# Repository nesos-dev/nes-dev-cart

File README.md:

# NES-DEV-CART

Open-source FPGA development cartridge for the Nintendo Entertainment System. **v4.1** — now with 8MB onboard PSRAM.

Plugs into a real NES. Programs over USB-C. Debug via UART. Full NES bus access. 39 SMT components, professionally assembled.

## What Is It

NES-DEV-CART is a cartridge-shaped PCB that replaces the ROM chip with a modern FPGA. It gives your FPGA bidirectional access to every signal on the NES 72-pin cartridge connector — CPU bus, PPU bus, CIC, expansion port — all level-shifted between 5V and 3.3V.

An onboard FT2232HL provides USB-C JTAG programming and UART debug console. No external programmer needed.

## Specs

| | |
|---|---|
| **FPGA** | Sipeed Tang Primer 25K (Gowin GW5A-25, 25K LUTs) |
| **ROM Storage** | 8MB SPI PSRAM |
| **USB** | FT2232HL — Ch.A: JTAG, Ch.B: UART debug |
| **Level Shifting** | 4x 74ALVC164245DGG (bidirectional 5V-3.3V) |
| **NES Signals** | CPU A0-A14, D0-D7, PPU A0-A13, D0-D7, CIC, IRQ, EXP |
| **PCB** | 4-layer, 1.6mm, ENIG, gold fingers, L-shaped |
| **Connector** | 72-pin NES edge connector (30-degree bevel) |
| **FPGA Connection** | 2x DF40C-60DS 0.4mm B2B connectors |

## What You Can Build

- **Homebrew games** — test on real hardware, not emulators
- **Custom mappers** — design mapper chips in Verilog that never existed
- **Flash cartridge** — load ROMs from USB, run on real NES
- **Bus analyzer** — sniff CPU/PPU traffic in real time via UART
- **Expansion audio** — VRC6, Sunsoft 5B style audio hardware
- **Hardware research** — study NES bus behavior at the signal level

## Repository Structure

```
hardware/
├── nes-dev-cart.kicad_pcb      KiCad PCB layout
├── nes-dev-cart.kicad_sch      KiCad schematic
├── nes-dev-cart.kicad_pro      KiCad project
├── footprints/                 Custom footprint libraries
├── shell/                     Cart shell STL files (front/back)
└── production/
    ├── nes-dev-cart-gerbers.zip    Fabrication-ready gerbers
    ├── nes-dev-cart-bom.csv        BOM with LCSC part numbers
    ├── nes-dev-cart-cpl-jlcpcb.csv Component placement list
    ├── README-assembly.md          Assembly instructions
    ├── nes-dev-cart-render-*.png   Board renders (top/bottom)
    └── gerbers/                    Individual gerber files

website/                        Product website (nesos.dev)
├── index.html
├── style.css
└── success.html
```

## Ordering PCBs

Upload `hardware/production/nes-dev-cart-gerbers.zip` to JLCPCB:

- Layers: 4
- Thickness: 1.6mm
- Surface finish: ENIG
- Gold fingers: Yes, 30-degree bevel
- Assembly: Both sides (DF40 connectors on bottom)

Upload `nes-dev-cart-bom.csv` and `nes-dev-cart-cpl-jlcpcb.csv` for SMT assembly. See `production/README-assembly.md` for details.

## Requirements

- NES front-loader console (NES-001)
- Sipeed Tang Primer 25K module
- USB-C cable
- Gowin IDE or Yosys/nextpnr for FPGA development

## License

Hardware: GPL-3.0

NES-DEV-CART is an independent project not affiliated with or endorsed by Nintendo.

## Links

- Website: https://nesos.dev

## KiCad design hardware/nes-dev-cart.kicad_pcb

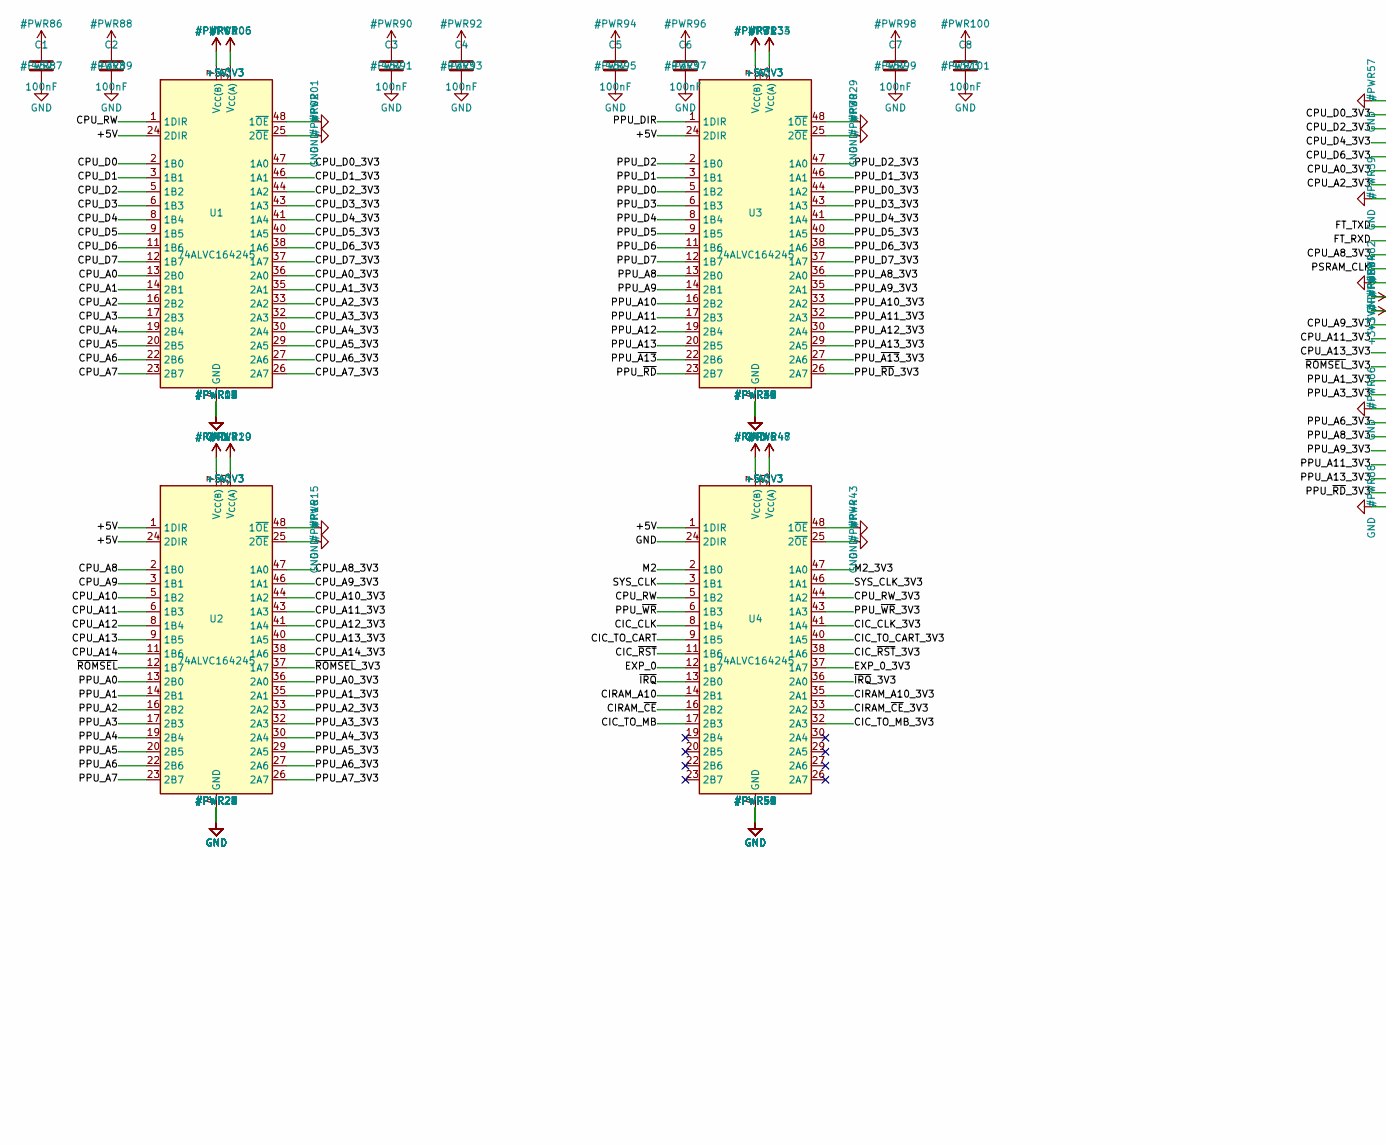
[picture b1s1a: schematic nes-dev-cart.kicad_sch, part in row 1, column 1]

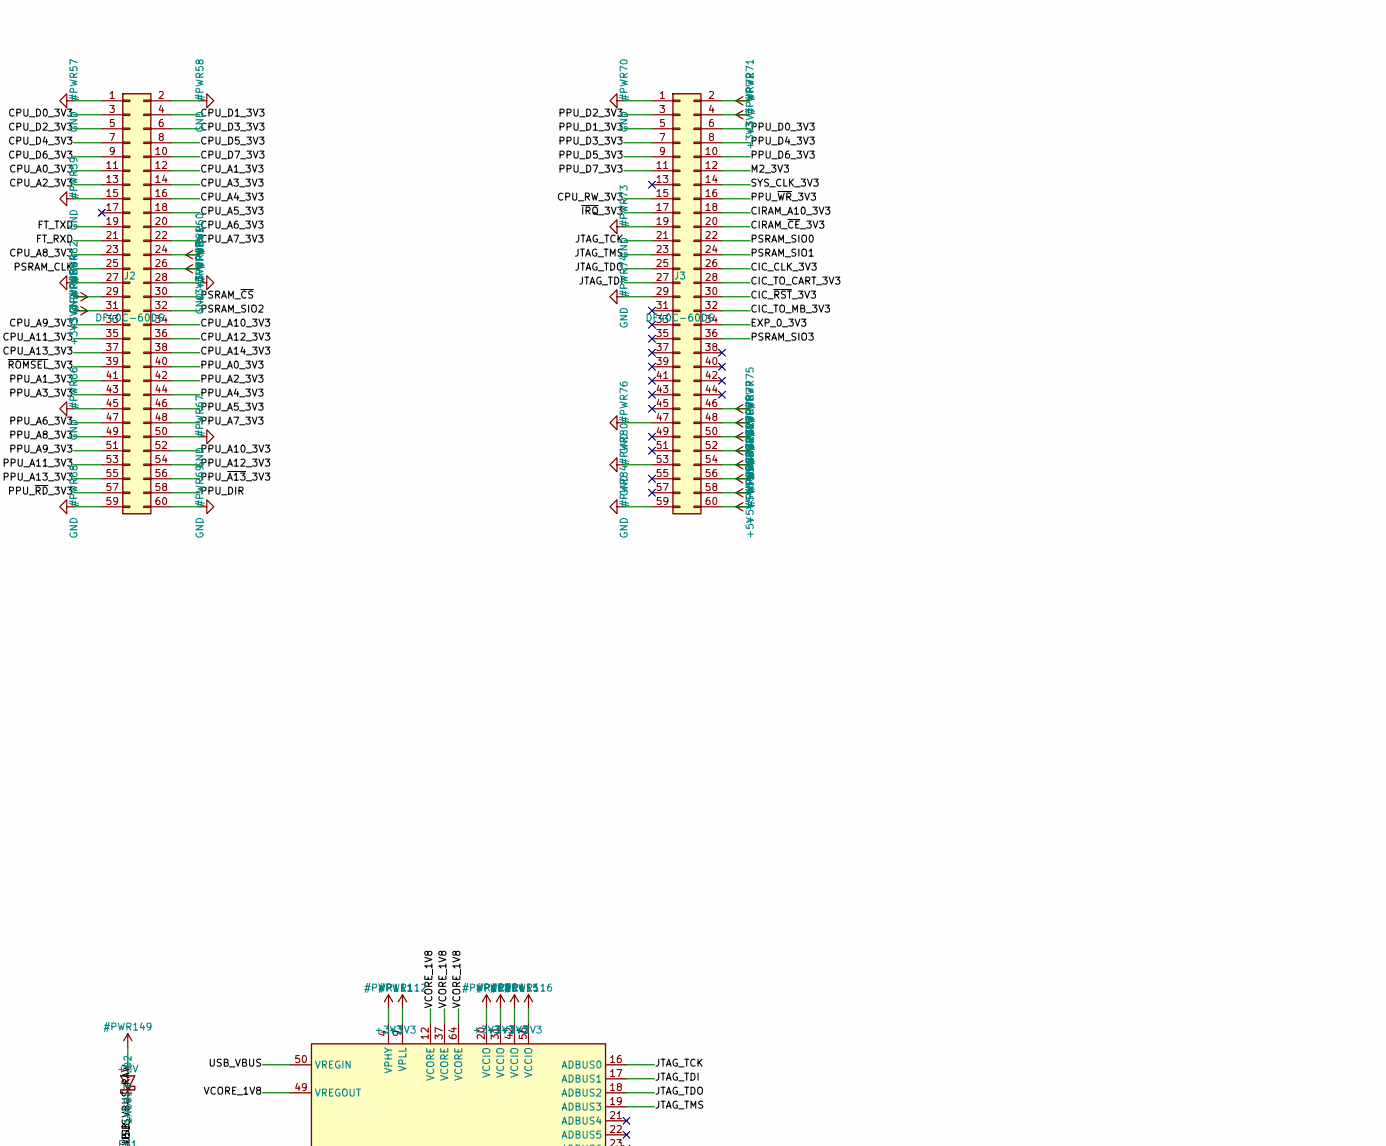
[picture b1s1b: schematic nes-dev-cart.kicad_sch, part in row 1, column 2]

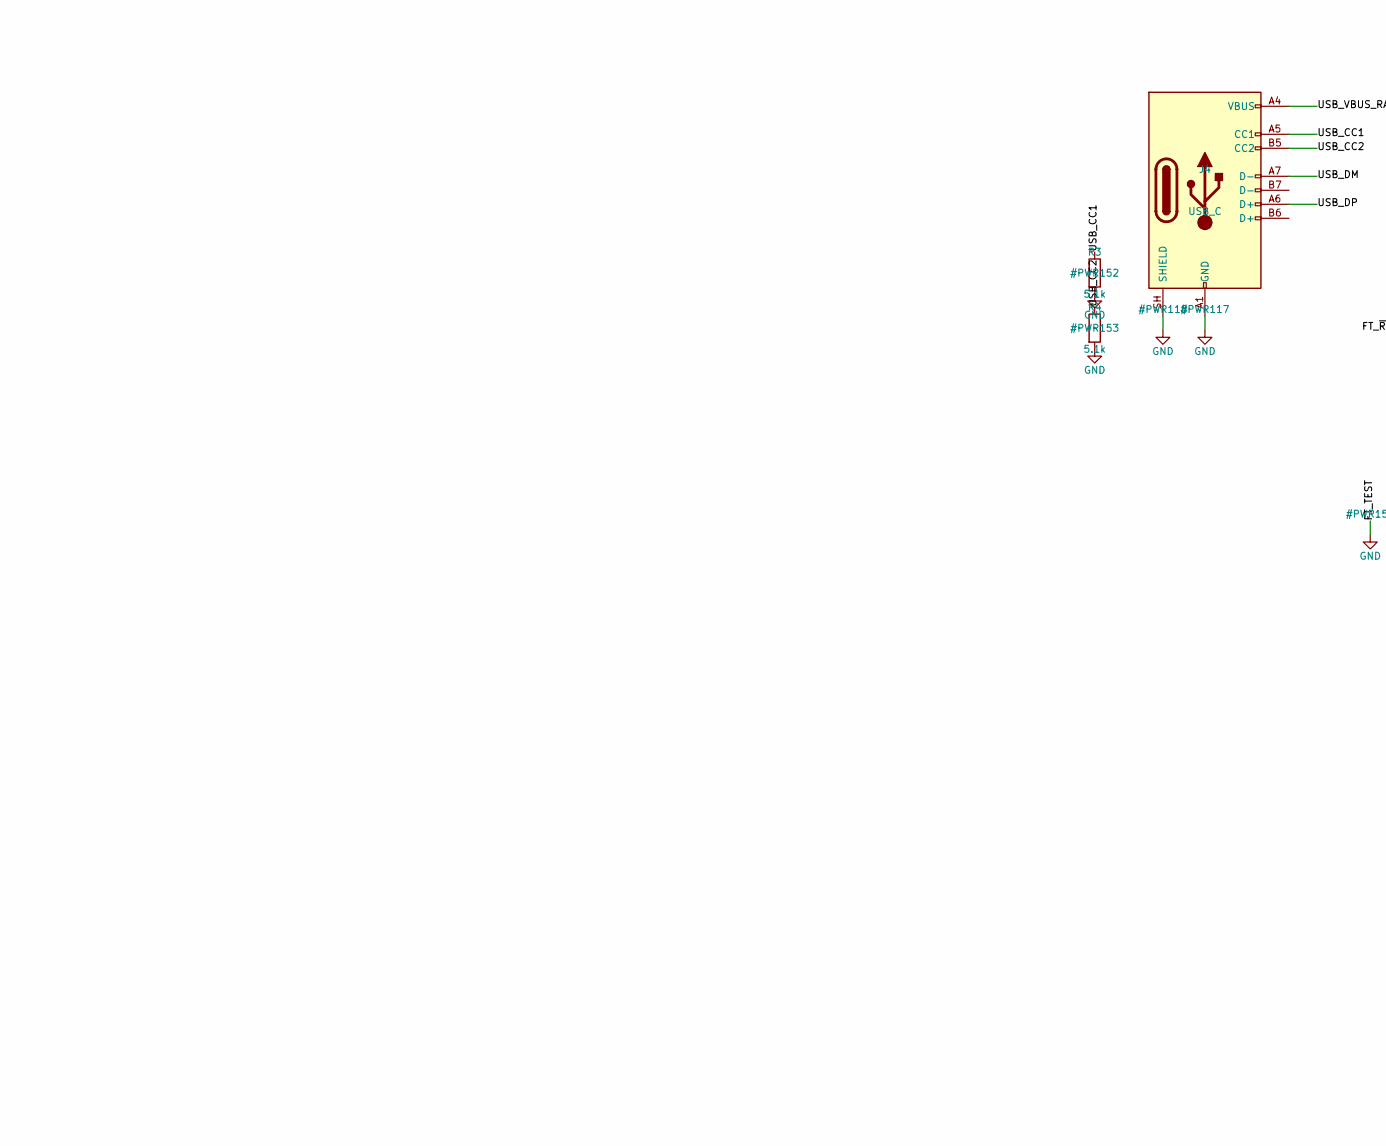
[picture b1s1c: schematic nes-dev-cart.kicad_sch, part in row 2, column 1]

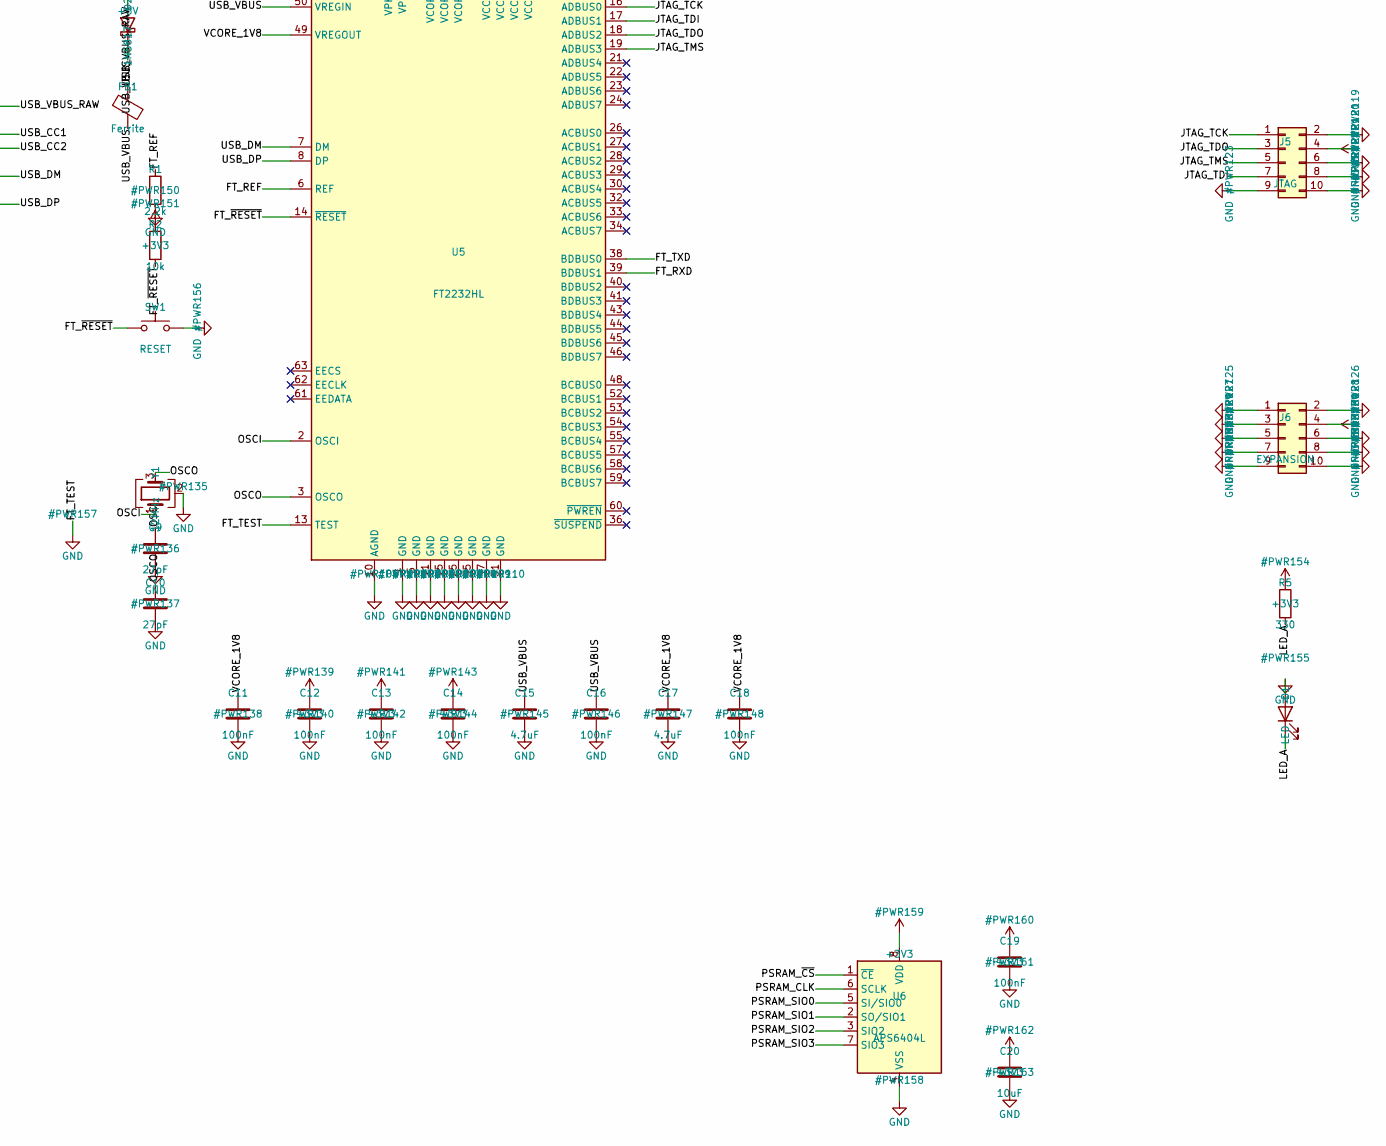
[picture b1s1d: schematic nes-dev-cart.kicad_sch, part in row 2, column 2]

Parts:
C1, C2, C3, C4, C5, C6, C7, C8, C11, C12, C13, C14, C16, C18, C19: 100nF
C9, C10: 27pF
C15, C17: 4.7uF
C20: 10uF
D1: LED
D2: 1N5817
FB1: Ferrite
J2, J3: DF40C-60DS
J4: USB_C
J5: JTAG
J6: EXPANSION
R1: 2.2k
R2: 10k
R3, R4: 5.1k
R5: 330
SW1: RESET
U1, U2, U3, U4: 74ALVC164245
U5: FT2232HL
U6: APS6404L
Y1: 12MHz

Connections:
+3V3: C2.1, C4.1, C6.1, C8.1, C12.1, C13.1, C14.1, C19.1, C20.1, J2.24, J2.26, J2.29, J2.31, J3.2, J3.4, J3.46, J3.48, J3.50, J5.4, J6.4, R2.1, R5.1, U1.31 (V_{CC(A)}), U1.42 (V_{CC(A)}), U2.31 (V_{CC(A)}), U2.42 (V_{CC(A)}), U3.31 (V_{CC(A)}), U3.42 (V_{CC(A)}), U4.31 (V_{CC(A)}), U4.42 (V_{CC(A)}), U5.4 (VPHY), U5.9 (VPLL), U5.20 (VCCIO), U5.31 (VCCIO), U5.42 (VCCIO), U5.56 (VCCIO), U6.8 (VDD)
+5V: C1.1, C3.1, C5.1, C7.1, D2.2 (A), J3.52, J3.54, J3.56, J3.58, J3.60, U1.7 (V_{CC(B)}), U1.18 (V_{CC(B)}), U1.24 (2DIR), U2.1 (1DIR), U2.7 (V_{CC(B)}), U2.18 (V_{CC(B)}), U2.24 (2DIR), U3.7 (V_{CC(B)}), U3.18 (V_{CC(B)}), U3.24 (2DIR), U4.1 (1DIR), U4.7 (V_{CC(B)}), U4.18 (V_{CC(B)}); also elsewhere on the board
/CIC_CLK: U4.8 (1B4); also elsewhere on the board
/CIC_CLK_3V3: J3.26, U4.41 (1A4)
/CIC_TO_CART: U4.9 (1B5); also elsewhere on the board
/CIC_TO_CART_3V3: J3.28, U4.40 (1A5)
/CIC_TO_MB: U4.17 (2B3); also elsewhere on the board
/CIC_TO_MB_3V3: J3.32, U4.32 (2A3)
/CIC_~RST: U4.11 (1B6); also elsewhere on the board
/CIC_~RST_3V3: J3.30, U4.38 (1A6)
/CIRAM_A10: U4.14 (2B1); also elsewhere on the board
/CIRAM_A10_3V3: J3.18, U4.35 (2A1)
/CIRAM_~CE: U4.16 (2B2); also elsewhere on the board
/CIRAM_~CE_3V3: J3.20, U4.33 (2A2)
/CPU_A0: U1.13 (2B0); also elsewhere on the board
/CPU_A0_3V3: J2.11, U1.36 (2A0)
/CPU_A1: U1.14 (2B1); also elsewhere on the board
/CPU_A1_3V3: J2.12, U1.35 (2A1)
/CPU_A2: U1.16 (2B2); also elsewhere on the board
/CPU_A2_3V3: J2.13, U1.33 (2A2)
/CPU_A3: U1.17 (2B3); also elsewhere on the board
/CPU_A3_3V3: J2.14, U1.32 (2A3)
/CPU_A4: U1.19 (2B4); also elsewhere on the board
/CPU_A4_3V3: J2.16, U1.30 (2A4)
/CPU_A5: U1.20 (2B5); also elsewhere on the board
/CPU_A5_3V3: J2.18, U1.29 (2A5)
/CPU_A6: U1.22 (2B6); also elsewhere on the board
/CPU_A6_3V3: J2.20, U1.27 (2A6)
/CPU_A7: U1.23 (2B7); also elsewhere on the board
/CPU_A7_3V3: J2.22, U1.26 (2A7)
/CPU_A8: U2.2 (1B0); also elsewhere on the board
/CPU_A8_3V3: J2.23, U2.47 (1A0)
/CPU_A9: U2.3 (1B1); also elsewhere on the board
/CPU_A9_3V3: J2.33, U2.46 (1A1)
/CPU_A10: U2.5 (1B2); also elsewhere on the board
/CPU_A10_3V3: J2.34, U2.44 (1A2)
/CPU_A11: U2.6 (1B3); also elsewhere on the board
/CPU_A11_3V3: J2.35, U2.43 (1A3)
/CPU_A12: U2.8 (1B4); also elsewhere on the board
/CPU_A12_3V3: J2.36, U2.41 (1A4)
/CPU_A13: U2.9 (1B5); also elsewhere on the board
/CPU_A13_3V3: J2.37, U2.40 (1A5)
/CPU_A14: U2.11 (1B6); also elsewhere on the board
/CPU_A14_3V3: J2.38, U2.38 (1A6)
/CPU_D0: U1.2 (1B0); also elsewhere on the board
/CPU_D0_3V3: J2.3, U1.47 (1A0)
/CPU_D1: U1.3 (1B1); also elsewhere on the board
/CPU_D1_3V3: J2.4, U1.46 (1A1)
/CPU_D2: U1.5 (1B2); also elsewhere on the board
/CPU_D2_3V3: J2.5, U1.44 (1A2)
/CPU_D3: U1.6 (1B3); also elsewhere on the board
/CPU_D3_3V3: J2.6, U1.43 (1A3)
/CPU_D4: U1.8 (1B4); also elsewhere on the board
/CPU_D4_3V3: J2.7, U1.41 (1A4)
/CPU_D5: U1.9 (1B5); also elsewhere on the board
/CPU_D5_3V3: J2.8, U1.40 (1A5)
/CPU_D6: U1.11 (1B6); also elsewhere on the board
/CPU_D6_3V3: J2.9, U1.38 (1A6)
/CPU_D7: U1.12 (1B7); also elsewhere on the board
/CPU_D7_3V3: J2.10, U1.37 (1A7)
/CPU_RW: U1.1 (1DIR), U4.5 (1B2); also elsewhere on the board
/CPU_RW_3V3: J3.15, U4.44 (1A2)
/EXP_0: U4.12 (1B7); also elsewhere on the board
/EXP_0_3V3: J3.34, U4.37 (1A7)
/FT_REF: R1.1, U5.6 (REF)
/FT_RXD: J2.21, U5.39 (BDBUS1)
/FT_TXD: J2.19, U5.38 (BDBUS0)
/FT_~RESET: R2.2, SW1.1, U5.14 (~RESET)
/JTAG_TCK: J3.21, J5.1, U5.16 (ADBUS0)
/JTAG_TDI: J3.27, J5.7, U5.17 (ADBUS1)
/JTAG_TDO: J3.25, J5.3, U5.18 (ADBUS2)
/JTAG_TMS: J3.23, J5.5, U5.19 (ADBUS3)
/LED_A: D1.1 (K), R5.2
/M2: U4.2 (1B0); also elsewhere on the board
/M2_3V3: J3.12, U4.47 (1A0)
/OSCI: C9.1, U5.2 (OSCI), Y1.1
/OSCO: C10.1, U5.3 (OSCO), Y1.3
/PPU_A0: U2.13 (2B0); also elsewhere on the board
/PPU_A0_3V3: J2.40, U2.36 (2A0)
/PPU_A1: U2.14 (2B1); also elsewhere on the board
/PPU_A1_3V3: J2.41, U2.35 (2A1)
/PPU_A2: U2.16 (2B2); also elsewhere on the board
/PPU_A2_3V3: J2.42, U2.33 (2A2)
/PPU_A3: U2.17 (2B3); also elsewhere on the board
/PPU_A3_3V3: J2.43, U2.32 (2A3)
/PPU_A4: U2.19 (2B4); also elsewhere on the board
/PPU_A4_3V3: J2.44, U2.30 (2A4)
/PPU_A5: U2.20 (2B5); also elsewhere on the board
/PPU_A5_3V3: J2.46, U2.29 (2A5)
/PPU_A6: U2.22 (2B6); also elsewhere on the board
/PPU_A6_3V3: J2.47, U2.27 (2A6)
/PPU_A7: U2.23 (2B7); also elsewhere on the board
/PPU_A7_3V3: J2.48, U2.26 (2A7)
/PPU_A8: U3.13 (2B0); also elsewhere on the board
/PPU_A8_3V3: J2.49, U3.36 (2A0)
/PPU_A9: U3.14 (2B1); also elsewhere on the board
/PPU_A9_3V3: J2.51, U3.35 (2A1)
/PPU_A10: U3.16 (2B2); also elsewhere on the board
/PPU_A10_3V3: J2.52, U3.33 (2A2)
/PPU_A11: U3.17 (2B3); also elsewhere on the board
/PPU_A11_3V3: J2.53, U3.32 (2A3)
/PPU_A12: U3.19 (2B4); also elsewhere on the board
/PPU_A12_3V3: J2.54, U3.30 (2A4)
/PPU_A13: U3.20 (2B5); also elsewhere on the board
/PPU_A13_3V3: J2.55, U3.29 (2A5)
/PPU_D0: U3.5 (1B2); also elsewhere on the board
/PPU_D0_3V3: J3.6, U3.44 (1A2)
/PPU_D1: U3.3 (1B1); also elsewhere on the board
/PPU_D1_3V3: J3.5, U3.46 (1A1)
/PPU_D2: U3.2 (1B0); also elsewhere on the board
/PPU_D2_3V3: J3.3, U3.47 (1A0)
/PPU_D3: U3.6 (1B3); also elsewhere on the board
/PPU_D3_3V3: J3.7, U3.43 (1A3)
/PPU_D4: U3.8 (1B4); also elsewhere on the board
/PPU_D4_3V3: J3.8, U3.41 (1A4)
/PPU_D5: U3.9 (1B5); also elsewhere on the board
/PPU_D5_3V3: J3.9, U3.40 (1A5)
/PPU_D6: U3.11 (1B6); also elsewhere on the board
/PPU_D6_3V3: J3.10, U3.38 (1A6)
/PPU_D7: U3.12 (1B7); also elsewhere on the board
/PPU_D7_3V3: J3.11, U3.37 (1A7)
/PPU_DIR: J2.58, U3.1 (1DIR)
/PPU_~A13: U3.22 (2B6); also elsewhere on the board
/PPU_~A13_3V3: J2.56, U3.27 (2A6)
/PPU_~RD: U3.23 (2B7); also elsewhere on the board
/PPU_~RD_3V3: J2.57, U3.26 (2A7)
/PPU_~WR: U4.6 (1B3); also elsewhere on the board
/PPU_~WR_3V3: J3.16, U4.43 (1A3)
/PSRAM_CLK: J2.25, U6.6 (SCLK)
/PSRAM_SIO0: J3.22, U6.5 (SI/SIO0)
/PSRAM_SIO1: J3.24, U6.2 (SO/SIO1)
/PSRAM_SIO2: J2.32, U6.3 (SIO2)
/PSRAM_SIO3: J3.36, U6.7 (SIO3)
/PSRAM_~CS: J2.30, U6.1 (~CE)
/SYS_CLK: U4.3 (1B1); also elsewhere on the board
/SYS_CLK_3V3: J3.14, U4.46 (1A1)
/USB_CC1: J4.A5 (CC1), R3.1
/USB_CC2: J4.B5 (CC2), R4.1
/USB_DM: J4.A7 (D-), U5.7 (DM)
/USB_DP: J4.A6 (D+), U5.8 (DP)
/USB_VBUS: C15.1, C16.1, D2.1 (K), FB1.2, U5.50 (VREGIN)
/USB_VBUS_RAW: FB1.1, J4.A4 (VBUS), J4.A9 (VBUS), J4.B4 (VBUS), J4.B9 (VBUS)
/VCORE_1V8: C11.1, C17.1, C18.1, U5.12 (VCORE), U5.37 (VCORE), U5.49 (VREGOUT), U5.64 (VCORE)
/~IRQ: U4.13 (2B0); also elsewhere on the board
/~IRQ_3V3: J3.17, U4.36 (2A0)
/~ROMSEL: U2.12 (1B7); also elsewhere on the board
/~ROMSEL_3V3: J2.39, U2.37 (1A7)
GND: C1.2, C2.2, C3.2, C4.2, C5.2, C6.2, C7.2, C8.2, C9.2, C10.2, C11.2, C12.2, C13.2, C14.2, C15.2, C16.2, C17.2, C18.2, C19.2, C20.2, D1.2 (A), J2.1, J2.2, J2.15, J2.27, J2.28, J2.45, J2.50, J2.59, J2.60, J3.1, J3.19, J3.29, J3.47, J3.53, J3.59, J4.A1 (GND), J4.A12 (GND), J4.B1 (GND), J4.B12 (GND), J4.SH (SHIELD), J5.2, J5.6, J5.8, J5.9, J5.10, J6.1, J6.2, J6.3, J6.5, J6.6, J6.7, J6.8, J6.9, J6.10, R1.2, R3.2, R4.2, SW1.2, U1.4 (GND), U1.10 (GND), U1.15 (GND), U1.21 (GND), U1.25 (2~OE), U1.28 (GND), U1.34 (GND), U1.39 (GND), U1.45 (GND), U1.48 (1~OE), U2.4 (GND), U2.10 (GND), U2.15 (GND), U2.21 (GND), U2.25 (2~OE), U2.28 (GND), U2.34 (GND), U2.39 (GND), U2.45 (GND), U2.48 (1~OE), U3.4 (GND), U3.10 (GND), U3.15 (GND), U3.21 (GND), U3.25 (2~OE), U3.28 (GND), U3.34 (GND), U3.39 (GND), U3.45 (GND), U3.48 (1~OE), U4.4 (GND), U4.10 (GND), U4.15 (GND), U4.21 (GND), U4.24 (2DIR), U4.25 (2~OE), U4.28 (GND), U4.34 (GND), U4.39 (GND), U4.45 (GND), U4.48 (1~OE), U5.1 (GND), U5.5 (GND), U5.10 (AGND), U5.11 (GND), U5.13 (TEST), U5.15 (GND), U5.25 (GND), U5.35 (GND), U5.47 (GND), U5.51 (GND), U6.4 (VSS), Y1.2 (G), Y1.4 (G); also elsewhere on the board

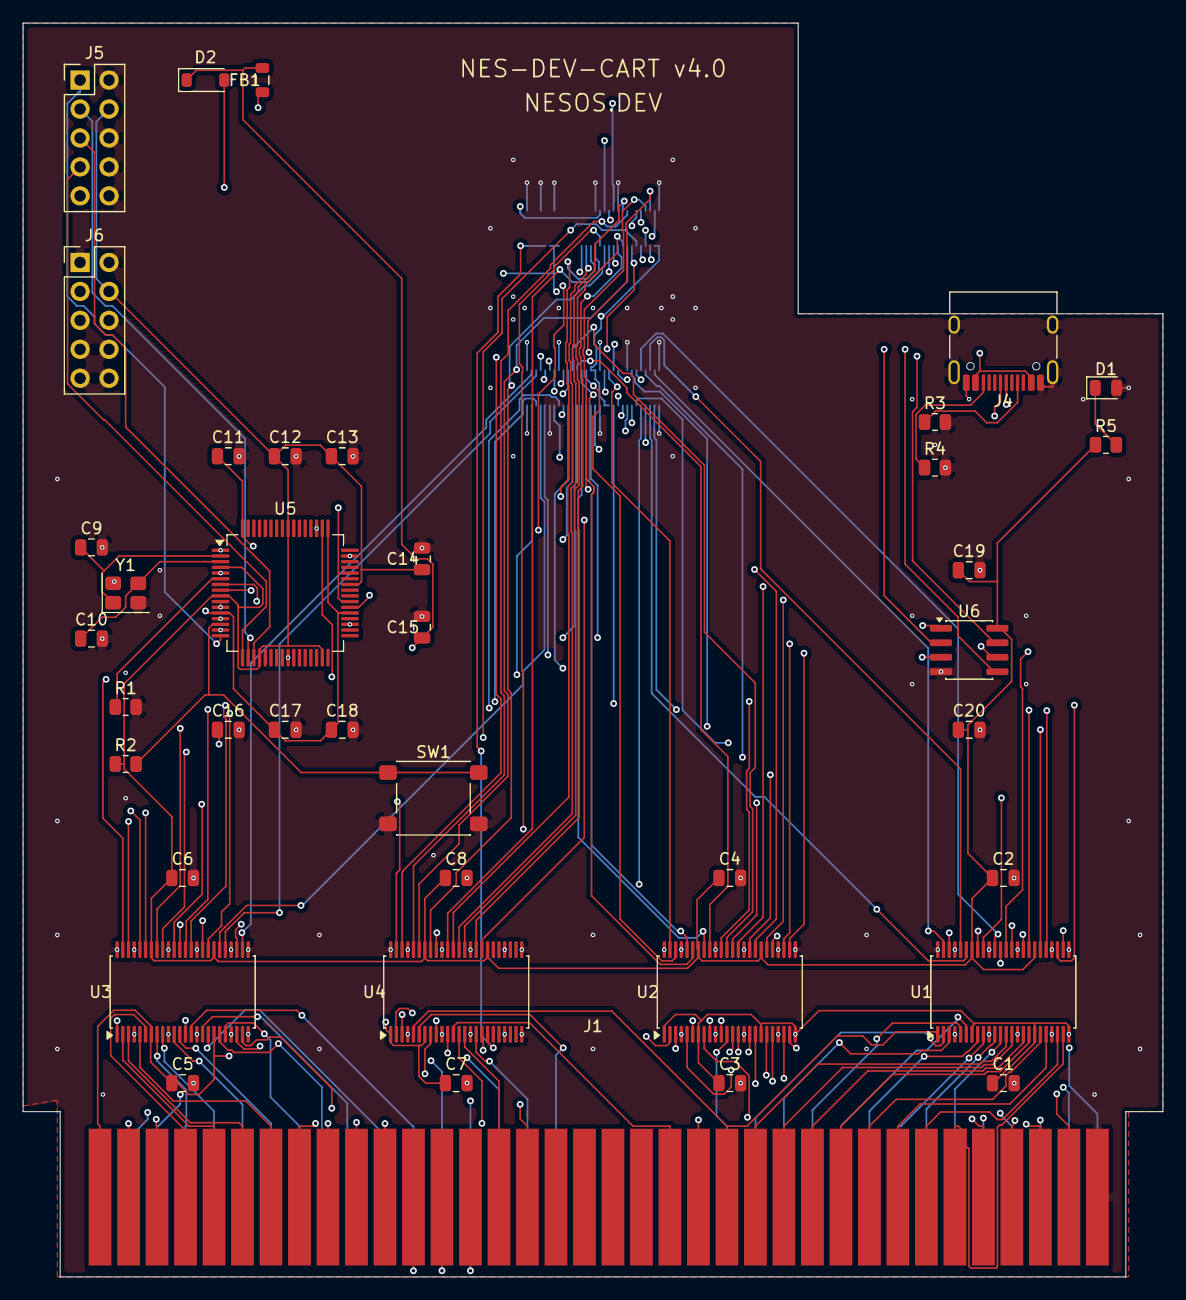
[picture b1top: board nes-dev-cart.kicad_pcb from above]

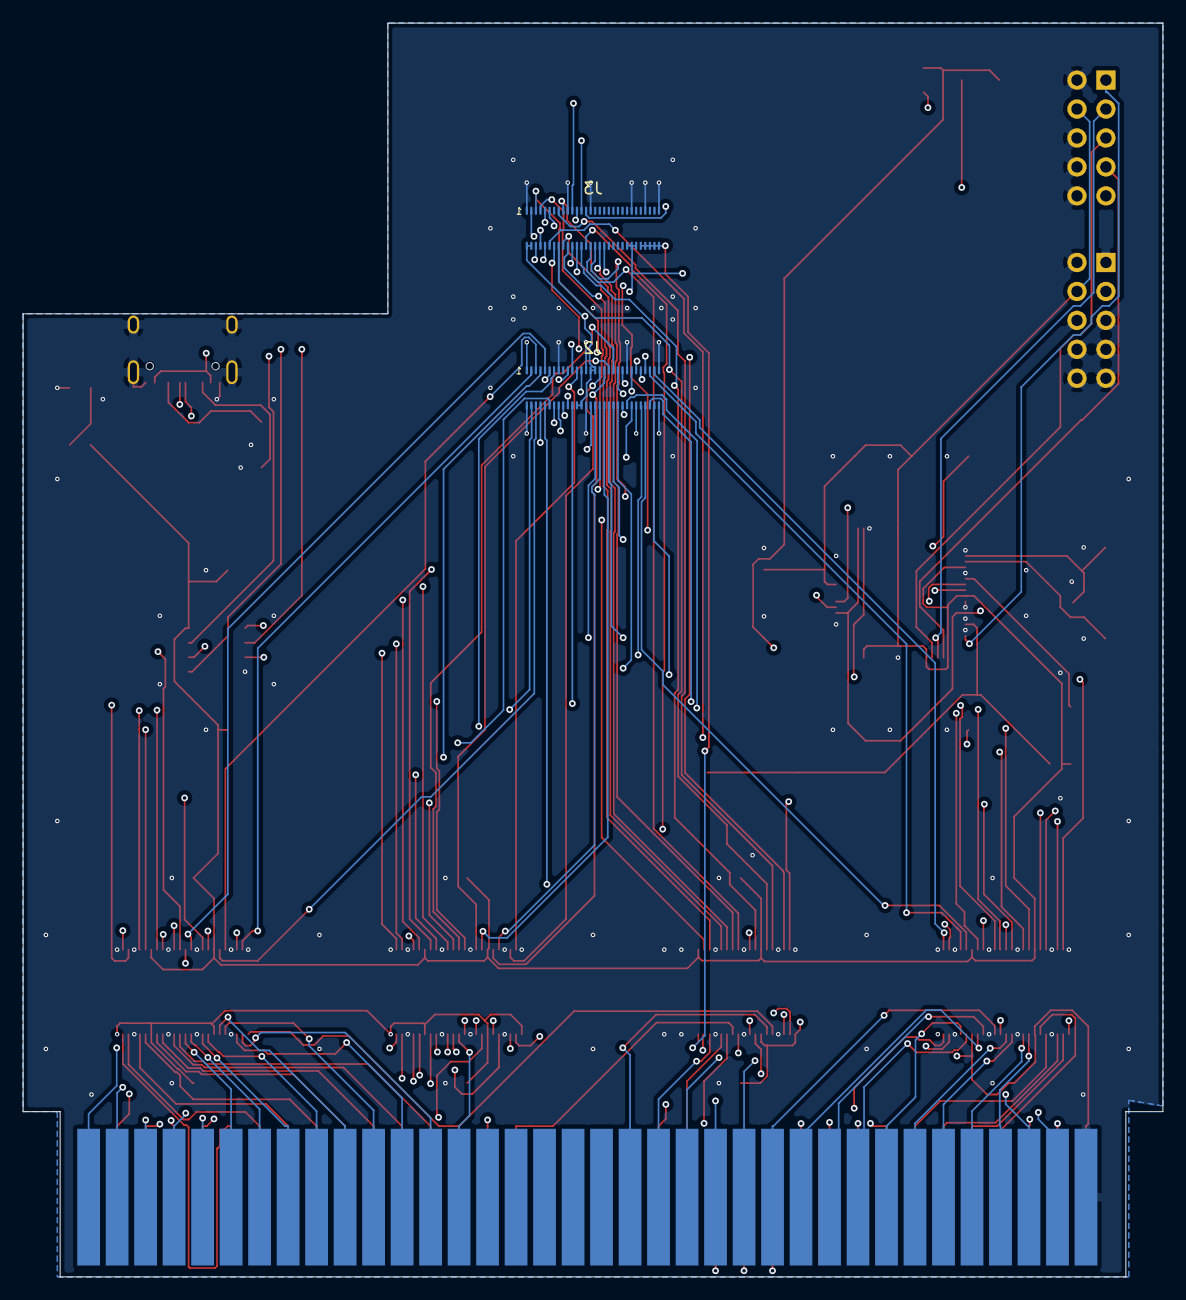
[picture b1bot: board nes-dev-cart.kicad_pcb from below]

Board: 4 copper layers, 100.0 x 110.0 mm, 42 parts (2 on the bottom side), 148 nets.

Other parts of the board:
J1: NES_72Pin; NES_72Pin_CardEdge

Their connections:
+5V: J1.36; also elsewhere on the board
/CIC_CLK: J1.70; also elsewhere on the board
/CIC_TO_CART: J1.34; also elsewhere on the board
/CIC_TO_MB: J1.35; also elsewhere on the board
/CIC_~RST: J1.71; also elsewhere on the board
/CIRAM_A10: J1.22; also elsewhere on the board
/CIRAM_~CE: J1.57; also elsewhere on the board
/CPU_A0: J1.13; also elsewhere on the board
/CPU_A1: J1.12; also elsewhere on the board
/CPU_A2: J1.11; also elsewhere on the board
/CPU_A3: J1.10; also elsewhere on the board
/CPU_A4: J1.9; also elsewhere on the board
/CPU_A5: J1.8; also elsewhere on the board
/CPU_A6: J1.7; also elsewhere on the board
/CPU_A7: J1.6; also elsewhere on the board
/CPU_A8: J1.5; also elsewhere on the board
/CPU_A9: J1.4; also elsewhere on the board
/CPU_A10: J1.3; also elsewhere on the board
/CPU_A11: J1.2; also elsewhere on the board
/CPU_A12: J1.39; also elsewhere on the board
/CPU_A13: J1.40; also elsewhere on the board
/CPU_A14: J1.41; also elsewhere on the board
/CPU_D0: J1.49; also elsewhere on the board
/CPU_D1: J1.48; also elsewhere on the board
/CPU_D2: J1.47; also elsewhere on the board
/CPU_D3: J1.46; also elsewhere on the board
/CPU_D4: J1.45; also elsewhere on the board
/CPU_D5: J1.44; also elsewhere on the board
/CPU_D6: J1.43; also elsewhere on the board
/CPU_D7: J1.42; also elsewhere on the board
/CPU_RW: J1.14; also elsewhere on the board
/EXP_0: J1.16; also elsewhere on the board
/M2: J1.38; also elsewhere on the board
/PPU_A0: J1.29; also elsewhere on the board
/PPU_A1: J1.28; also elsewhere on the board
/PPU_A2: J1.27; also elsewhere on the board
/PPU_A3: J1.26; also elsewhere on the board
/PPU_A4: J1.25; also elsewhere on the board
/PPU_A5: J1.24; also elsewhere on the board
/PPU_A6: J1.23; also elsewhere on the board
/PPU_A7: J1.59; also elsewhere on the board
/PPU_A8: J1.60; also elsewhere on the board
/PPU_A9: J1.61; also elsewhere on the board
/PPU_A10: J1.63; also elsewhere on the board
/PPU_A11: J1.62; also elsewhere on the board
/PPU_A12: J1.64; also elsewhere on the board
/PPU_A13: J1.65; also elsewhere on the board
/PPU_D0: J1.30; also elsewhere on the board
/PPU_D1: J1.31; also elsewhere on the board
/PPU_D2: J1.32; also elsewhere on the board
/PPU_D3: J1.33; also elsewhere on the board
/PPU_D4: J1.69; also elsewhere on the board
/PPU_D5: J1.68; also elsewhere on the board
/PPU_D6: J1.67; also elsewhere on the board
/PPU_D7: J1.66; also elsewhere on the board
/PPU_~A13: J1.58; also elsewhere on the board
/PPU_~RD: J1.21; also elsewhere on the board
/PPU_~WR: J1.56; also elsewhere on the board
/SYS_CLK: J1.37; also elsewhere on the board
/~IRQ: J1.15; also elsewhere on the board
/~ROMSEL: J1.50; also elsewhere on the board
GND: J1.1, J1.72; also elsewhere on the board

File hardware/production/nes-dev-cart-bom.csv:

Comment,Designator,Footprint,LCSC Part #
100nF 50V X7R,"C1,C2,C3,C4,C5,C6,C7,C8,C11,C12,C13,C14,C16,C18,C19",C_0805_2012Metric,C49678
27pF 50V NP0,"C9,C10",C_0805_2012Metric,C107113
4.7uF 25V X5R,"C15,C17",C_0805_2012Metric,C1779
2.2k 1%,R1,R_0805_2012Metric,C17520
10k 1%,R2,R_0805_2012Metric,C17414
5.1k 1%,"R3,R4",R_0805_2012Metric,C27834
330R 1%,R5,R_0805_2012Metric,C17630
74ALVC164245DGG,"U1,U2,U3,U4",TSSOP-48_6.1x12.5mm_P0.5mm,C5531
FT2232HL,U5,LQFP-64_10x10mm_P0.5mm,C27882
12MHz Crystal,Y1,Crystal_SMD_3225-4Pin_3.2x2.5mm,C390764
Ferrite 600R@100MHz,FB1,L_0805_2012Metric,C21286
Green LED,D1,LED_0805_2012Metric,C2297
1N5817W Schottky,D2,D_SOD-123,C571353
USB-C 16P Receptacle,J4,USB_C_Receptacle_HRO_TYPE-C-31-M-12,C165948
DF40C-60DS-0.4V(51),"J2,J3",Hirose_DF40C-60DS-0.4V_2x30_P0.4mm,C597938
PTS645SM43SMTR92LFS,SW1,SW_SPST_PTS645,C221880
APS6404L-3SQR-SN 8MB PSRAM,U6,SOIC-8_3.9x4.9mm_P1.27mm,C5333729
10uF 25V X5R,C20,C_0805_2012Metric,C15850

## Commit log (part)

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2026-06-01 NES-DEV-CART v4.0: hardware design files and production outputs
2026-06-01 Remove website (moved to separate repo)
